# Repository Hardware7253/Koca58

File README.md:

# Lily58 Koca

A [Lily58](https://github.com/kata0510/Lily58) variant featuring SMT components, RJ45 interconnect and STM32F103 MCU.

## Pictures

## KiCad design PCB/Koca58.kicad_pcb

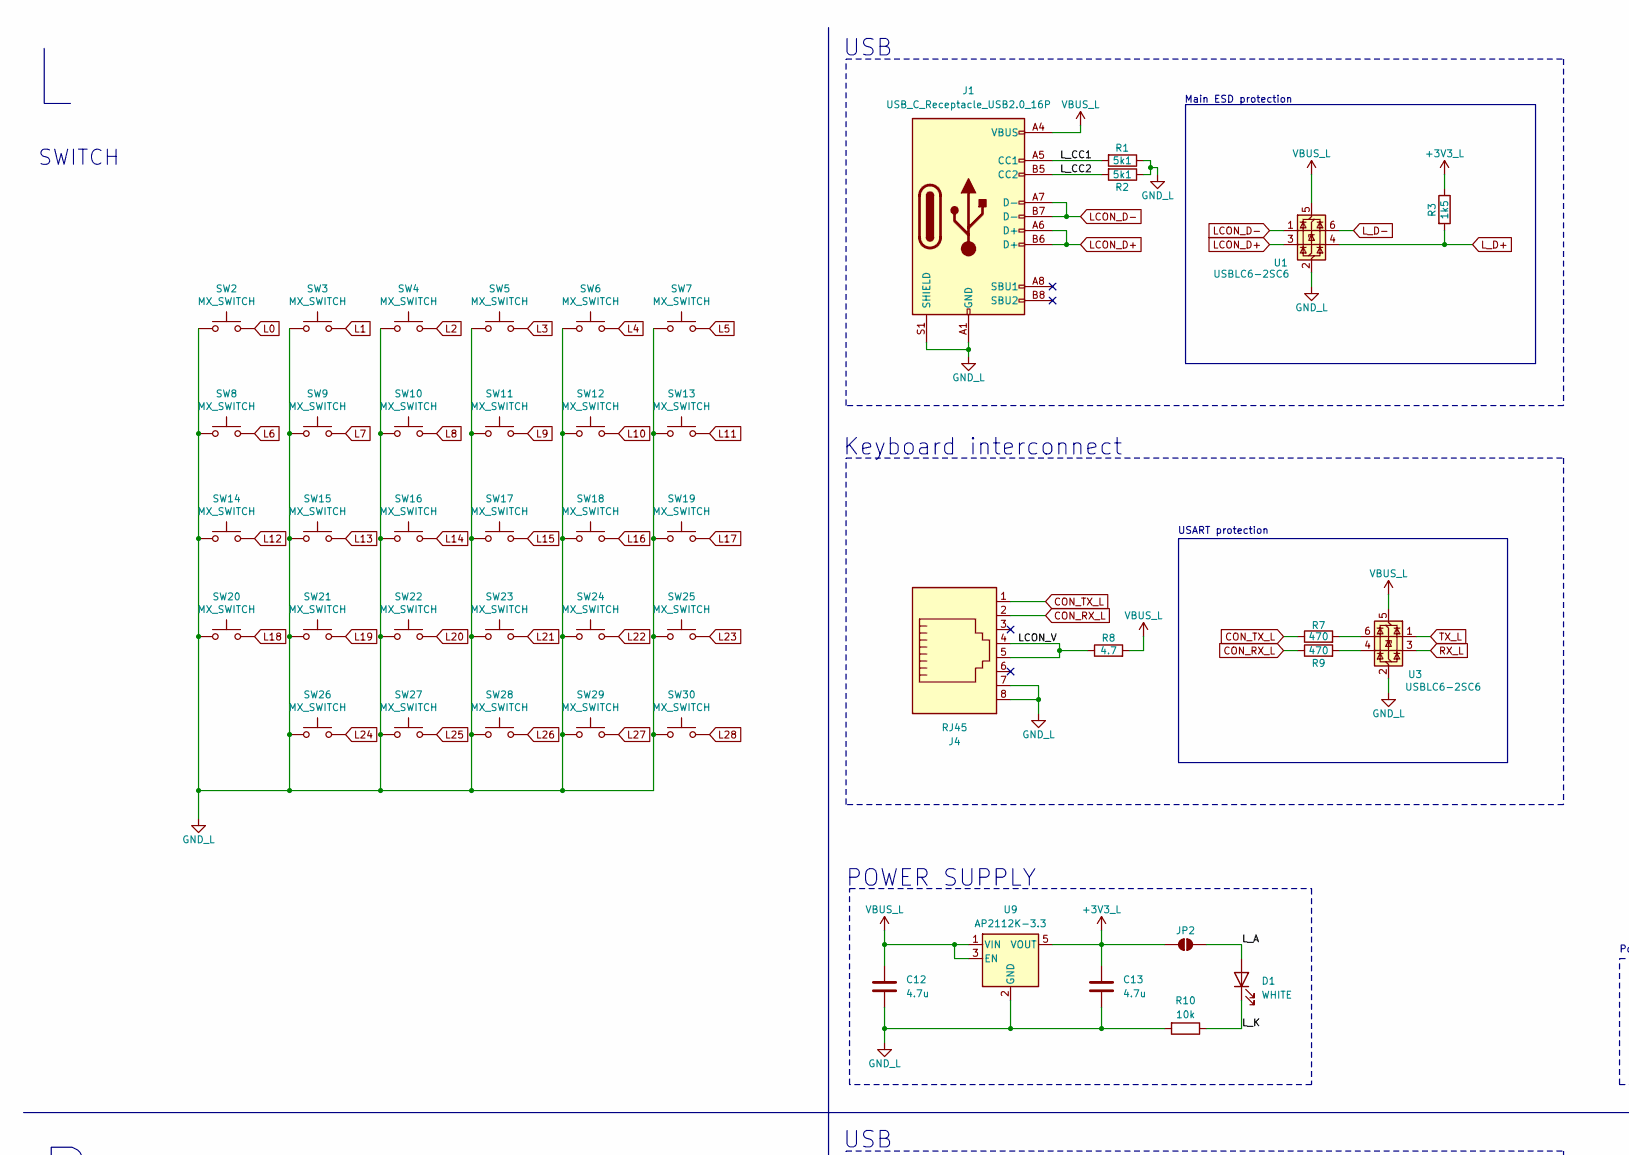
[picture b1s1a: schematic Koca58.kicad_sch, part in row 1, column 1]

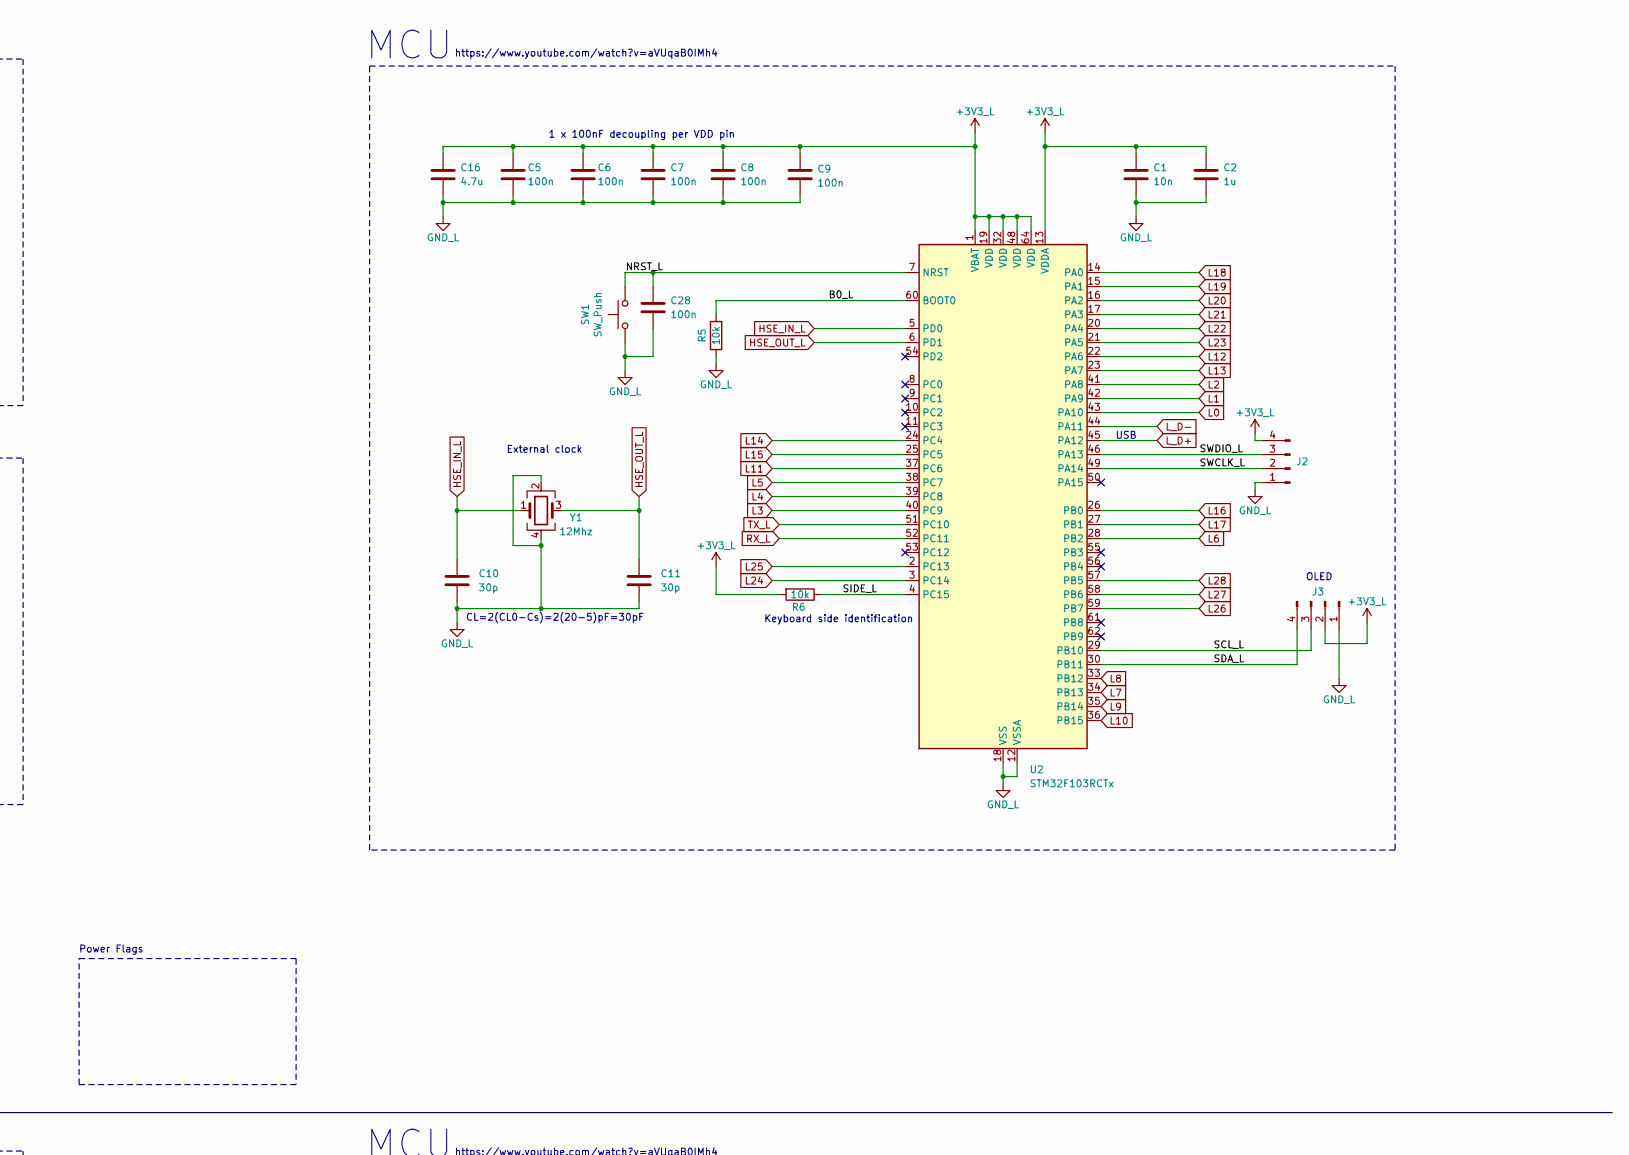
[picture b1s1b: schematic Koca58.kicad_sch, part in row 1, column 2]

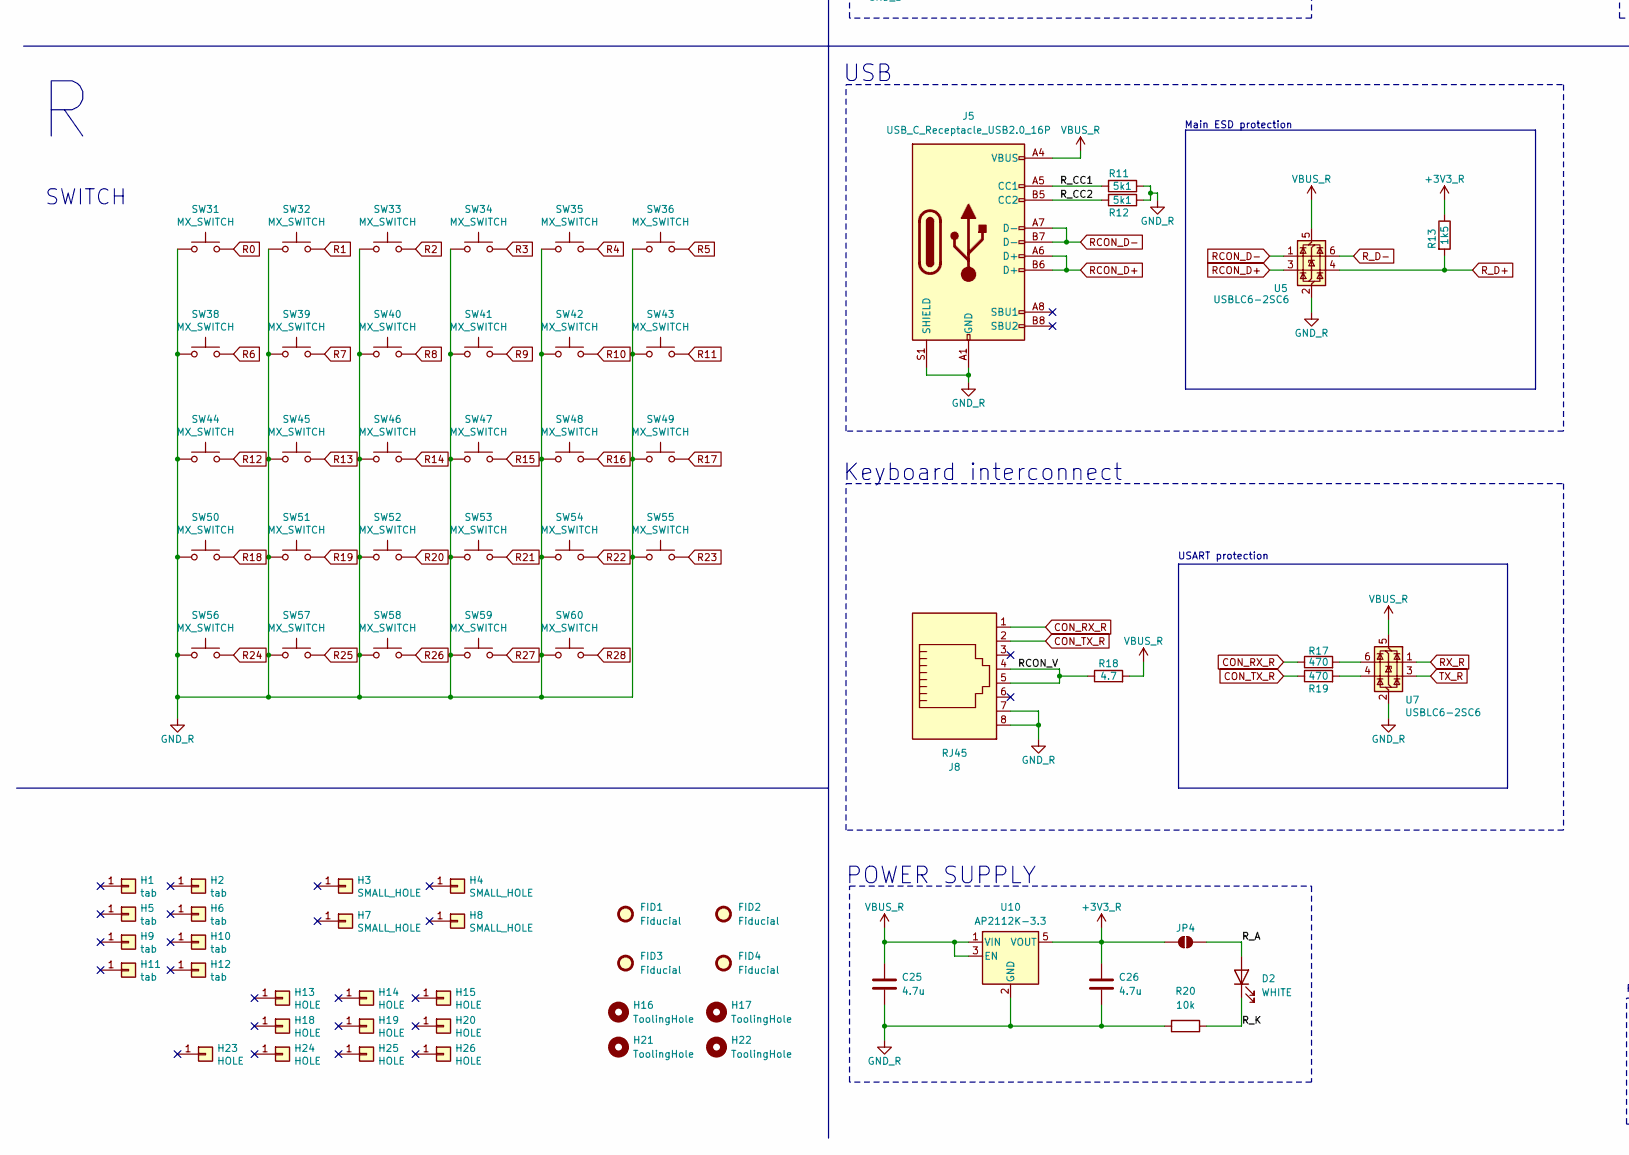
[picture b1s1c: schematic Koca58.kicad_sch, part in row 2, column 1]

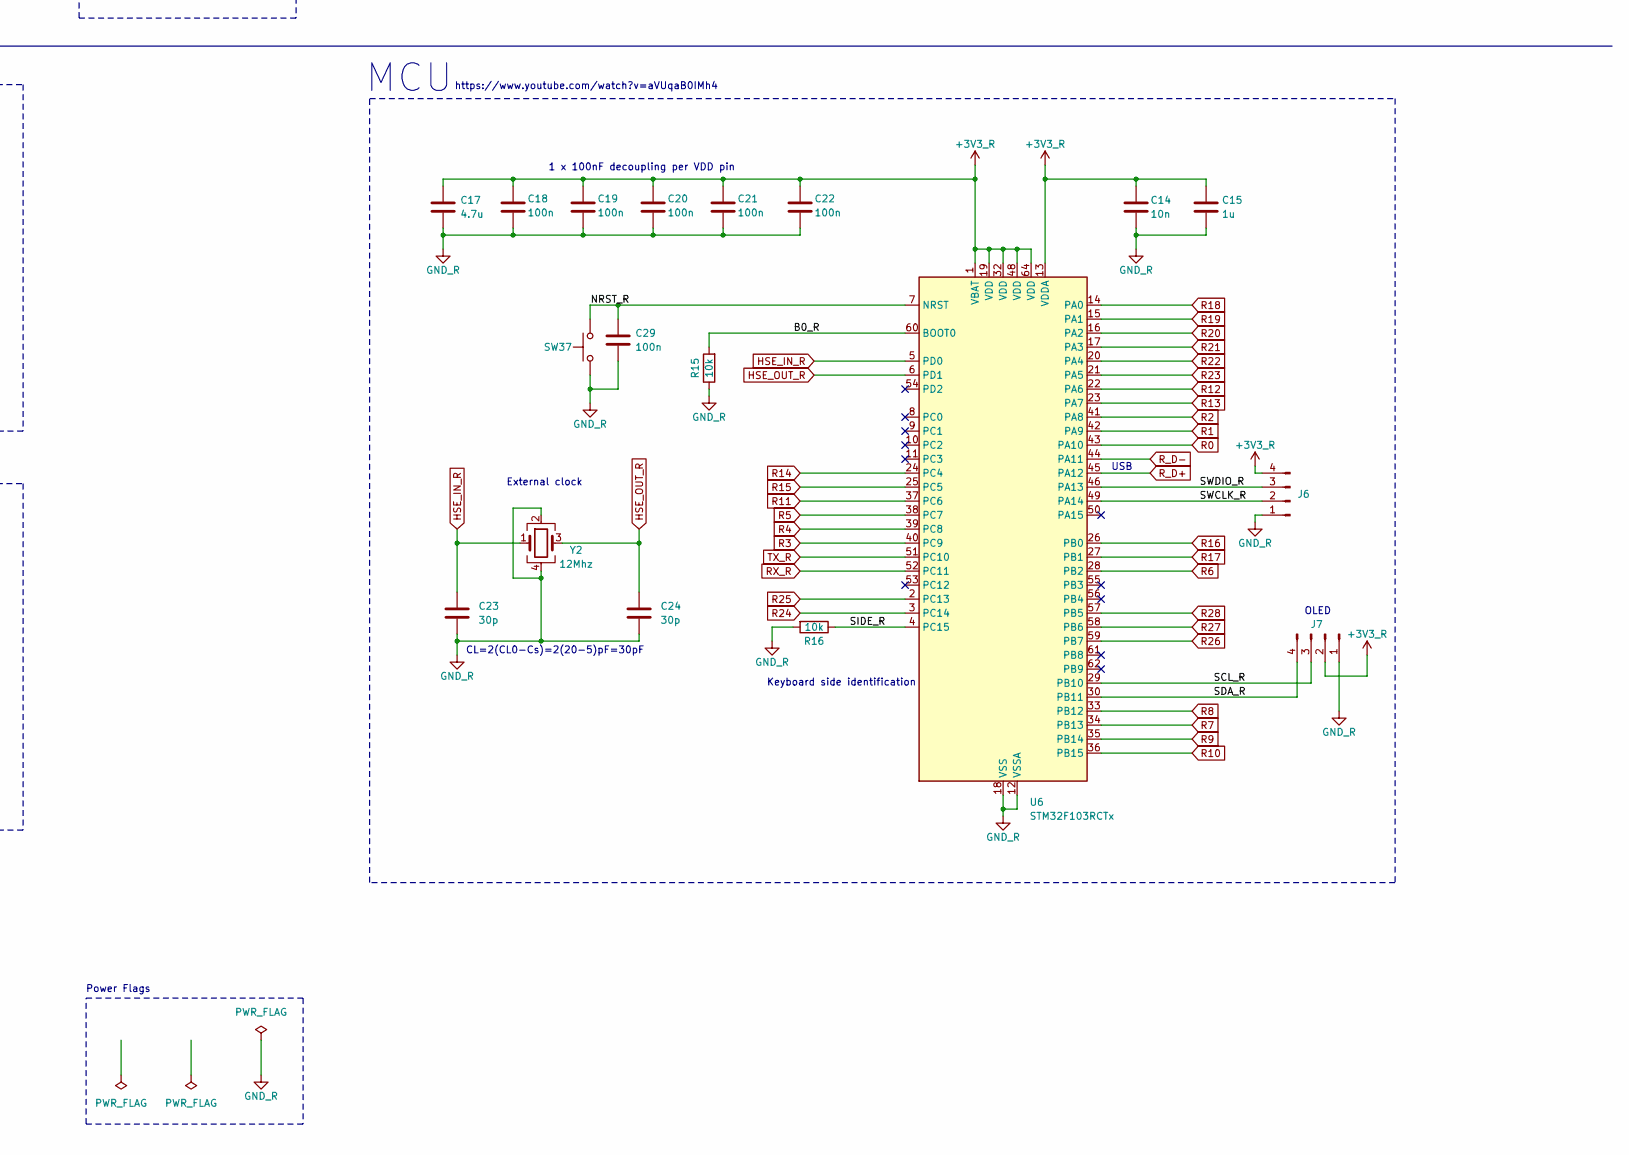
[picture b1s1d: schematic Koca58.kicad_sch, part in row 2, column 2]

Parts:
C1, C14: 10n; C_0402_1005Metric; Manufacturer Part Number CL05B103KB5NNNC; LCSC/JLC Part Number C15195
C2, C15: 1u; C_0402_1005Metric; Manufacturer Part Number CL05A105KA5NQNC; LCSC/JLC Part Number C52923
C5, C6, C7, C8, C9, C18, C19, C20, C21, C22, C28, C29: 100n; C_0402_1005Metric; Manufacturer Part Number CL05B104KO5NNNC; LCSC/JLC Part Number C1525
C10, C11, C23, C24: 30p; C_0402_1005Metric; Manufacturer Part Number 0402CG330J500NT; LCSC/JLC Part Number C1562
C12, C13, C16, C17, C25, C26: 4.7u; C_0603_1608Metric; Manufacturer Part Number CL10A475KO8NNNC; LCSC/JLC Part Number C19666
D1, D2: WHITE; LED_0603_1608Metric; Manufacturer Part Number KT-0603W; LCSC/JLC Part Number C2290
FID1, FID2, FID3, FID4: Fiducial; Fiducial_1mm_Mask2mm
H1, H2, H5, H6, H9, H10, H11, H12: tab; MouseBite
H3, H4, H7, H8: SMALL_HOLE; MountingHole_2.2mm_M2_Pad
H13, H14, H15, H18, H19, H20, H23, H24, H25, H26: HOLE; Standoff_Hole
H16, H17, H21, H22: ToolingHole; SMD_Tooling_Hole
J1, J5: USB_C_Receptacle_USB2.0_16P; USB_TYPE-C-31-M-12; Manufacturer Part Number TYPE-C-31-M-12; LCSC/JLC Part Number C165948
J2, J6: Conn_01x04_Pin; SWD_POGO_P1.27
J3, J7: Conn_01x04_Pin; PinHeader_1x04_P2.54mm_Vertical
J4, J8: RJ45; RJ45_Amphenol_54602-x08_Horizontal; Manufacturer Part Number 54602-908LF; LCSC/JLC Part Number C2847314
JP2, JP4: SolderJumper_2_Open; SolderJumper-2_P1.3mm_Bridged_Pad1.0x1.5mm
R1, R2, R11, R12: 5k1; R_0402_1005Metric; Manufacturer Part Number 0402WGF5101TCE; LCSC/JLC Part Number C25905
R3, R13: 1k5; R_0402_1005Metric; Manufacturer Part Number 0402WGF1501TCE; LCSC/JLC Part Number C25867
R5, R6, R10, R15, R16, R20: 10k; R_0402_1005Metric; Manufacturer Part Number 0402WGF1002TCE; LCSC/JLC Part Number C25744
R7, R9, R17, R19: 470; R_0402_1005Metric; Manufacturer Part Number 0402WGF4700TCE; LCSC/JLC Part Number C25117
R8, R18: 4.7; R_0603_1608Metric; Manufacturer Part Number 0603WAF470KT5E; LCSC/JLC Part Number C23164
SW1, SW37: SW_Push; Korean Hroparts Elec K2-1107ST-A4DW-06; Manufacturer Part Number K2-1107ST-A4DW-06; LCSC/JLC Part Number C118141
SW2, SW3, SW4, SW5, SW6, SW7, SW8, SW9, SW10, SW11, SW12, SW13, SW14, SW15, SW16, SW17, SW18, SW19, SW20, SW21, SW22, SW23, SW24, SW25, SW26, SW27, SW28, SW29, SW30, SW31, SW32, SW33, SW34, SW35, SW36, SW38, SW39, SW40, SW41, SW42, SW43, SW44, SW45, SW46, SW47, SW48, SW49, SW50, SW51, SW52, SW53, SW54, SW55, SW56, SW57, SW58, SW59, SW60: MX_SWITCH; MX_Hotswap; Manufacturer Part Number CPG151101S11-16; LCSC/JLC Part Number C41430893
U1, U3, U5, U7: USBLC6-2SC6; SOT-23-6; Manufacturer Part Number USBLC6-2SC6; LCSC/JLC Part Number C2687116
U2, U6: STM32F103RCTx; LQFP-64_10x10mm_P0.5mm; Manufacturer Part Number STM32F103RCT6; LCSC/JLC Part Number C8323
U9, U10: AP2112K-3.3; SOT-23-5; Manufacturer Part Number AP2112K-3.3TRG1; LCSC/JLC Part Number C51118
Y1, Y2: 12Mhz; Crystal_SMD_3225-4Pin_3.2x2.5mm; Manufacturer Part Number X322512MSB4SI; LCSC/JLC Part Number C9002

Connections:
+3V3_L: C1.1, C2.1, C5.1, C6.1, C7.1, C8.1, C9.1, C13.1, C16.1, J2.4, J3.2, JP2.1 (A), R3.1, R6.2, U2.1 (VBAT), U2.13 (VDDA), U2.19 (VDD), U2.32 (VDD), U2.48 (VDD), U2.64 (VDD), U9.5 (VOUT)
+3V3_R: C14.1, C15.1, C17.1, C18.1, C19.1, C20.1, C21.1, C22.1, C26.1, J6.4, J7.2, JP4.1 (A), R13.1, U6.1 (VBAT), U6.13 (VDDA), U6.19 (VDD), U6.32 (VDD), U6.48 (VDD), U6.64 (VDD), U10.5 (VOUT)
/B0_L: R5.2, U2.60 (BOOT0)
/B0_R: R15.2, U6.60 (BOOT0)
/LCON_V: J4.4, J4.5, R8.1
/L_A: D1.2 (A), JP2.2 (B)
/L_CC1: J1.A5 (CC1), R1.2
/L_CC2: J1.B5 (CC2), R2.2
/L_K: D1.1 (K), R10.1
/NRST_L: C28.1, SW1.2, U2.7 (NRST)
/NRST_R: C29.1, SW37.2, U6.7 (NRST)
/RCON_V: J8.4, J8.5, R18.1
/R_A: D2.2 (A), JP4.2 (B)
/R_CC1: J5.A5 (CC1), R11.2
/R_CC2: J5.B5 (CC2), R12.2
/R_K: D2.1 (K), R20.1
/SCL_L: J3.3, U2.29 (PB10)
/SCL_R: J7.3, U6.29 (PB10)
/SDA_L: J3.4, U2.30 (PB11)
/SDA_R: J7.4, U6.30 (PB11)
/SIDE_L: R6.1, U2.4 (PC15)
/SIDE_R: R16.1, U6.4 (PC15)
/SWCLK_L: J2.2, U2.49 (PA14)
/SWCLK_R: J6.2, U6.49 (PA14)
/SWDIO_L: J2.3, U2.46 (PA13)
/SWDIO_R: J6.3, U6.46 (PA13)
CON_RX_L: J4.2, R9.1
CON_RX_R: J8.1, R17.1
CON_TX_L: J4.1, R7.1
CON_TX_R: J8.2, R19.1
GND_L: C1.2, C2.2, C5.2, C6.2, C7.2, C8.2, C9.2, C10.2, C11.2, C12.2, C13.2, C16.2, C28.2, J1.A1 (GND), J1.A12 (GND), J1.B1 (GND), J1.B12 (GND), J1.S1 (SHIELD), J2.1, J3.1, J4.7, J4.8, R1.1, R2.1, R5.1, R10.2, SW1.1, SW2.1, SW3.1, SW4.1, SW5.1, SW6.1, SW7.1, SW8.1, SW9.1, SW10.1, SW11.1, SW12.1, SW13.1, SW14.1, SW15.1, SW16.1, SW17.1, SW18.1, SW19.1, SW20.1, SW21.1, SW22.1, SW23.1, SW24.1, SW25.1, SW26.1, SW27.1, SW28.1, SW29.1, SW30.1, U1.2 (GND), U2.12 (VSSA), U2.18 (VSS), U2.31 (VSS), U2.47 (VSS), U2.63 (VSS), U3.2 (GND), U9.2 (GND), Y1.2, Y1.4
GND_R: C14.2, C15.2, C17.2, C18.2, C19.2, C20.2, C21.2, C22.2, C23.2, C24.2, C25.2, C26.2, C29.2, J5.A1 (GND), J5.A12 (GND), J5.B1 (GND), J5.B12 (GND), J5.S1 (SHIELD), J6.1, J7.1, J8.7, J8.8, R11.1, R12.1, R15.1, R16.2, R20.2, SW31.1, SW32.1, SW33.1, SW34.1, SW35.1, SW36.1, SW37.1, SW38.1, SW39.1, SW40.1, SW41.1, SW42.1, SW43.1, SW44.1, SW45.1, SW46.1, SW47.1, SW48.1, SW49.1, SW50.1, SW51.1, SW52.1, SW53.1, SW54.1, SW55.1, SW56.1, SW57.1, SW58.1, SW59.1, SW60.1, U5.2 (GND), U6.12 (VSSA), U6.18 (VSS), U6.31 (VSS), U6.47 (VSS), U6.63 (VSS), U7.2 (GND), U10.2 (GND), Y2.2, Y2.4
HSE_IN_L: C10.1, U2.5 (PD0), Y1.1
HSE_IN_R: C23.1, U6.5 (PD0), Y2.1
HSE_OUT_L: C11.1, U2.6 (PD1), Y1.3
HSE_OUT_R: C24.1, U6.6 (PD1), Y2.3
L0: SW2.2, U2.43 (PA10)
L1: SW3.2, U2.42 (PA9)
L2: SW4.2, U2.41 (PA8)
L3: SW5.2, U2.40 (PC9)
L4: SW6.2, U2.39 (PC8)
L5: SW7.2, U2.38 (PC7)
L6: SW8.2, U2.28 (PB2)
L7: SW9.2, U2.34 (PB13)
L8: SW10.2, U2.33 (PB12)
L9: SW11.2, U2.35 (PB14)
L10: SW12.2, U2.36 (PB15)
L11: SW13.2, U2.37 (PC6)
L12: SW14.2, U2.22 (PA6)
L13: SW15.2, U2.23 (PA7)
L14: SW16.2, U2.24 (PC4)
L15: SW17.2, U2.25 (PC5)
L16: SW18.2, U2.26 (PB0)
L17: SW19.2, U2.27 (PB1)
L18: SW20.2, U2.14 (PA0)
L19: SW21.2, U2.15 (PA1)
L20: SW22.2, U2.16 (PA2)
L21: SW23.2, U2.17 (PA3)
L22: SW24.2, U2.20 (PA4)
L23: SW25.2, U2.21 (PA5)
L24: SW26.2, U2.3 (PC14)
L25: SW27.2, U2.2 (PC13)
L26: SW28.2, U2.59 (PB7)
L27: SW29.2, U2.58 (PB6)
L28: SW30.2, U2.57 (PB5)
LCON_D+: J1.A6 (D+), J1.B6 (D+), U1.3 (I/O2)
LCON_D-: J1.A7 (D-), J1.B7 (D-), U1.1 (I/O1)
L_D+: R3.2, U1.4 (I/O2), U2.45 (PA12)
L_D-: U1.6 (I/O1), U2.44 (PA11)
unnamed: R7.2, U3.6 (I/O1)
unnamed: R9.2, U3.4 (I/O2)
unnamed: R17.2, U7.6 (I/O1)
unnamed: R19.2, U7.4 (I/O2)
R0: SW31.2, U6.43 (PA10)
R1: SW32.2, U6.42 (PA9)
R2: SW33.2, U6.41 (PA8)
R3: SW34.2, U6.40 (PC9)
R4: SW35.2, U6.39 (PC8)
R5: SW36.2, U6.38 (PC7)
R6: SW38.2, U6.28 (PB2)
R7: SW39.2, U6.34 (PB13)
R8: SW40.2, U6.33 (PB12)
R9: SW41.2, U6.35 (PB14)
R10: SW42.2, U6.36 (PB15)
R11: SW43.2, U6.37 (PC6)
R12: SW44.2, U6.22 (PA6)
R13: SW45.2, U6.23 (PA7)
R14: SW46.2, U6.24 (PC4)
R15: SW47.2, U6.25 (PC5)
R16: SW48.2, U6.26 (PB0)
R17: SW49.2, U6.27 (PB1)
R18: SW50.2, U6.14 (PA0)
R19: SW51.2, U6.15 (PA1)
R20: SW52.2, U6.16 (PA2)
R21: SW53.2, U6.17 (PA3)
R22: SW54.2, U6.20 (PA4)
R23: SW55.2, U6.21 (PA5)
R24: SW56.2, U6.3 (PC14)
R25: SW57.2, U6.2 (PC13)
R26: SW58.2, U6.59 (PB7)
R27: SW59.2, U6.58 (PB6)
R28: SW60.2, U6.57 (PB5)
RCON_D+: J5.A6 (D+), J5.B6 (D+), U5.3 (I/O2)
RCON_D-: J5.A7 (D-), J5.B7 (D-), U5.1 (I/O1)
RX_L: U2.52 (PC11), U3.3 (I/O2)
RX_R: U6.52 (PC11), U7.1 (I/O1)
R_D+: R13.2, U5.4 (I/O2), U6.45 (PA12)
R_D-: U5.6 (I/O1), U6.44 (PA11)
TX_L: U2.51 (PC10), U3.1 (I/O1)
TX_R: U6.51 (PC10), U7.3 (I/O2)
VBUS_L: C12.1, J1.A4 (VBUS), J1.A9 (VBUS), J1.B4 (VBUS), J1.B9 (VBUS), R8.2, U1.5 (VBUS), U3.5 (VBUS), U9.1 (VIN), U9.3 (EN)
VBUS_R: C25.1, J5.A4 (VBUS), J5.A9 (VBUS), J5.B4 (VBUS), J5.B9 (VBUS), R18.2, U5.5 (VBUS), U7.5 (VBUS), U10.1 (VIN), U10.3 (EN)

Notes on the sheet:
1 x 100nF decoupling per VDD pin
USART protection
Keyboard interconnect
SWITCH
USB
CL=2(CL0-Cs)=2(20-5)pF=30pF
Main ESD protection
MCU
POWER SUPPLY
https://www.youtube.com/watch?v=aVUqaB0IMh4
OLED
Keyboard side identification
External clock
Power Flags

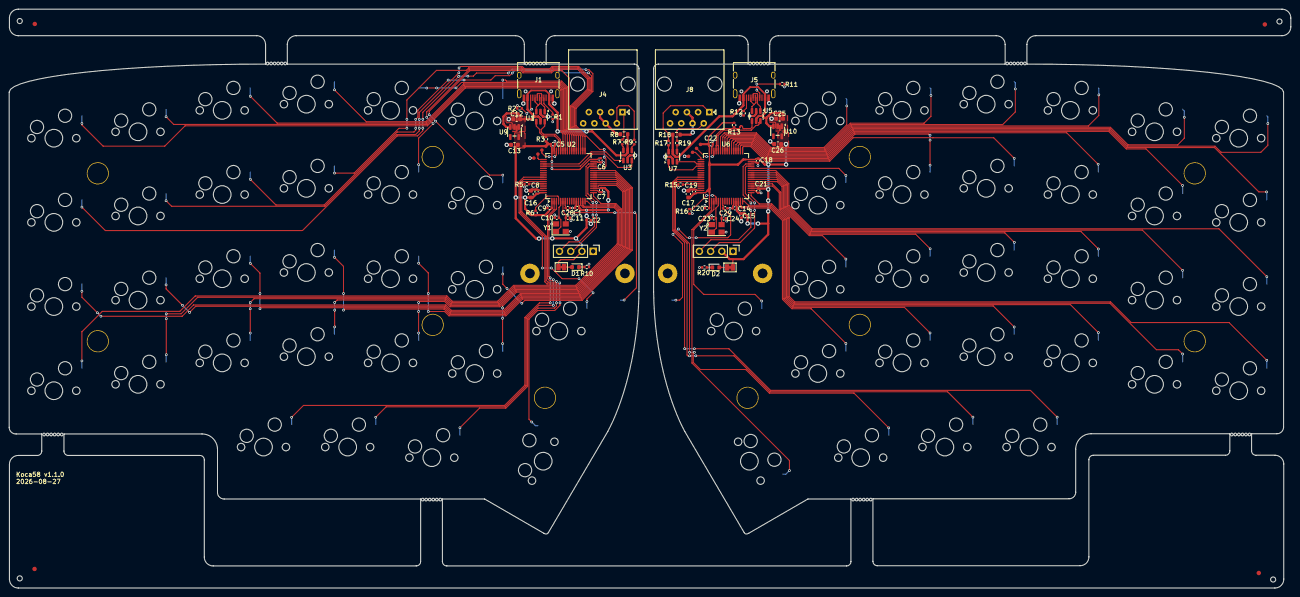
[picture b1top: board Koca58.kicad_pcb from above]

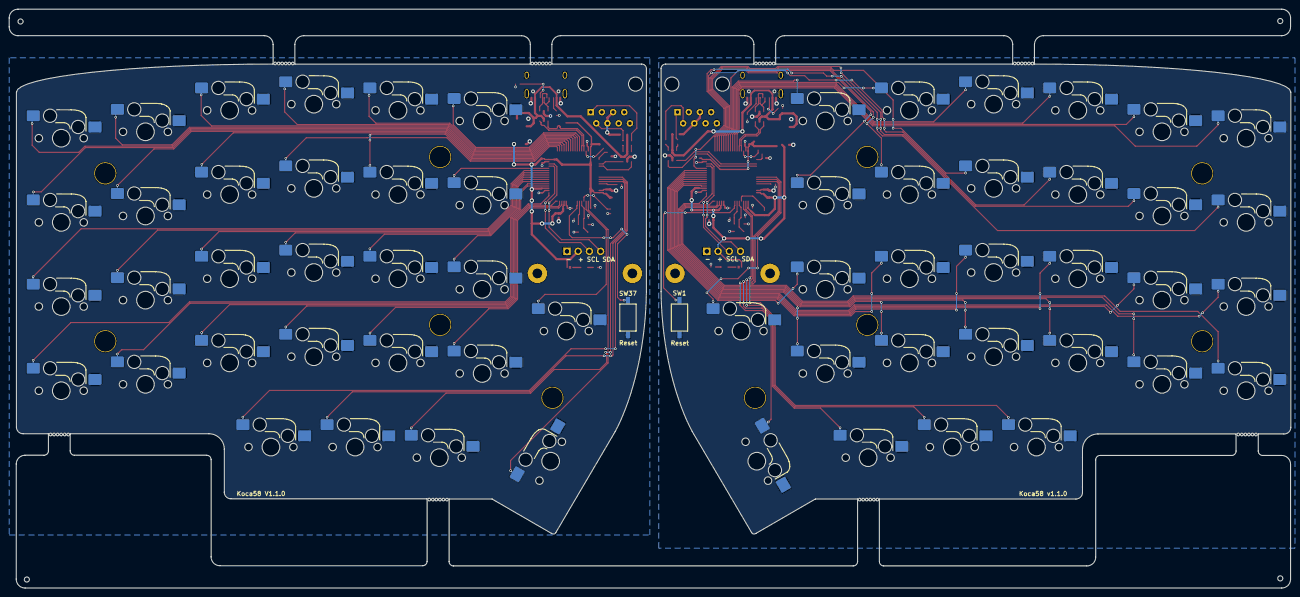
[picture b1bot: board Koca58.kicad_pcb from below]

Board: 2 copper layers, 290.1 x 131.0 mm, 156 parts (60 on the bottom side), 112 nets.

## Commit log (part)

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2025-01-21 First real commit
    Add KiCad design files and bootloader binary
2025-01-29 switch to direct matrix
2025-02-19 Prepared files for double sided PCBA
2025-02-28 Fixed PCBx BOM
    PCBx BOM listed the wrong crystal oscillator
2025-03-07 Improve via spacing
2025-04-14 Bout to imrpove hotplug protection
    Making a commit now because I have some new changes and I want something
    to fall back on if the new design changes suck.
2025-04-15 Added hotplugging protection to TRRS
    Technically added hotplugging protection. But it won't work because
    current isn't able to flow both directions in this design. It would
    require one side to always be the slave. But the hotplug protection for
    the master would then suck. So I'm about to try switch to USB-C for the
    interconnect.
2025-04-29 Switch to RJ45 Interconnects
2025-05-10 Renamed project
    Renamed project to Koca58 because it's now quite different to the
    Lily58. Also added fields to parts within KiCad so the python BOM
    generator could be removed.
2025-05-18 Added new case files
    Also did some minor changes to the main PCB
2025-05-27 Improved via to pad spacing
    Fab complained
2025-12-16 Updated case
2026-03-19 Update README with images
    Add pictures of the Lily58 Koca to README
